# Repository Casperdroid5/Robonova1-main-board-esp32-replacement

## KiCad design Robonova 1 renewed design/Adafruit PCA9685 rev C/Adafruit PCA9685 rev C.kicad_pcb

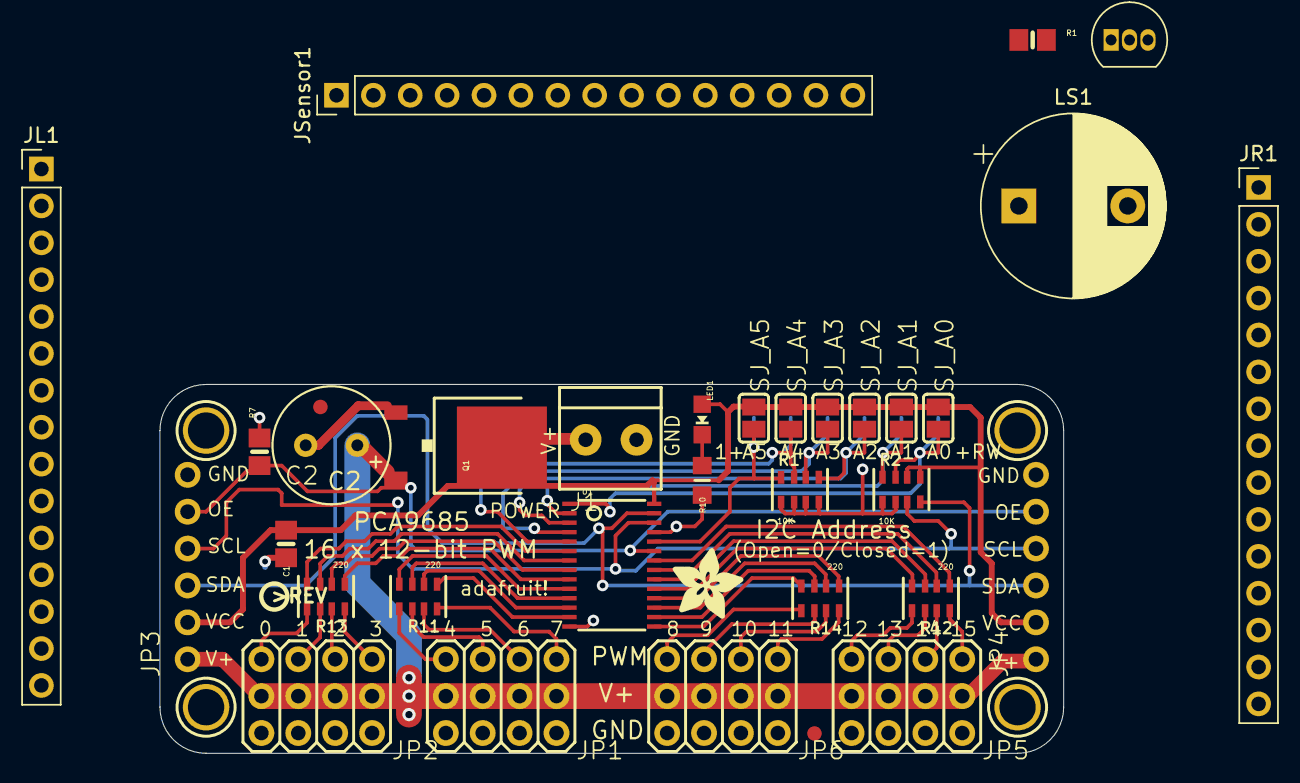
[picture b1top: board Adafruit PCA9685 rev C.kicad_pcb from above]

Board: 2 copper layers, 62.2 x 25.4 mm, 46 parts (0 on the bottom side), 63 nets.

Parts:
C1: 10uF; 0805-NO
C2: CPOL-USE3.5-8; E3,5-8
FID1, FID2: FIDUCIAL; FIDUCIAL_1MM
J1: TERMBLOCK_1X2; TERMBLOCK_1X2-3.5MM
JL1: Conn_01x15_Male; PinHeader_1x15_P2.54mm_Vertical
JP1, JP2, JP5, JP6: HEADER-3X04; 3X04
JP3, JP4: PINHD-1X6CB; 1X06-CLEANBIG
JR1: Conn_01x15_Male; PinHeader_1x15_P2.54mm_Vertical
JSensor1: Conn_01x15_Male; PinHeader_1x15_P2.54mm_Vertical
LED1: GREEN; CHIPLED_0805_NOOUTLINE
LS1: Speaker; CP_Radial_D12.5mm_P7.50mm
Q1: AOD417; TO252
Q2: BC547; TO-92_Inline
R1: 1K; 0805-NO
R1#2, R2: 10K; RESPACK_4X0603
R7: 10K; 0805-NO
R10: 470; _0805MP
R11, R12, R13, R14: 220; RESPACK_4X0603
SJ_A0, SJ_A1, SJ_A2, SJ_A3, SJ_A4, SJ_A5: SOLDERJUMPERREFLOW_NOPASTE; SOLDERJUMPER_REFLOW_NOPASTE
TP1, TP2, TP3, TP4, TP5, TP6: TESTPOINTROUND1MM; TESTPOINT_ROUND_1MM
U1: PCA9685; TSSOP28
U$47, U$48, U$49, U$50: MOUNTINGHOLE2.5; MOUNTINGHOLE_2.5_PLATED
U$51: ADAFRUIT_5MM
U$54: PCBFEAT-REV-040

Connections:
5.0V: C2.+, JP1.2, JP1.5, JP1.8, JP1.11, JP2.2, JP2.5, JP2.8, JP2.11, JP3.1, JP4.1, JP5.2, JP5.5, JP5.8, JP5.11, JP6.2, JP6.5, JP6.8, JP6.11, Q1.2
/3.3V: JL1.1, JSensor1.2, LS1.2
/A0: R2.7, SJ_A0.2, TP6.P$1, U1.1
/A1: R2.8, SJ_A1.2, TP5.P$1, U1.2
/A2: R1#2.5, SJ_A2.2, TP4.P$1
/A3: R1#2.6, SJ_A3.2, TP3.P$1
/A4: R1#2.7, SJ_A4.2, TP2.P$1
/A5: R1#2.8, SJ_A5.2, TP1.P$1
/CLK: JR1.5, JSensor1.9
/CS: JL1.3, JSensor1.10
/D2: JL1.4, JSensor1.6
/D4: JL1.5, JSensor1.5
/D18: JL1.9, JSensor1.11
/D19: JL1.10, JSensor1.12
/D23: JL1.15, JSensor1.13
/D25: JR1.8, JSensor1.14
/D26: JR1.7, JSensor1.15
/MISO: JR1.4, JSensor1.8
/MOSI: JR1.3, JSensor1.7
/OE: JP3.5, JP4.5, R7.1, U1.23
/PWM0: R13.4, U1.6
/PWM1: R13.3, U1.7
/PWM2: R13.2, U1.8
/PWM3: R13.1, U1.9
/PWM4: R11.4, U1.10
/PWM5: R11.3, U1.11
/PWM6: R11.2, U1.12
/PWM7: R11.1, U1.13
/PWM8: R14.4, U1.15
/PWM9: R14.3, U1.16
/PWM10: R14.2, U1.17
/PWM11: R14.1, U1.18
/PWM12: R12.4, U1.19
/PWM13: R12.3, U1.20
/PWM14: R12.2, U1.21
/PWM15: R12.1, U1.22
/Piezo: JR1.6, R1.2
/SCL: JP3.4, JP4.4, R2.3, U1.26
/SCL1: JR1.10, JSensor1.3
/SDA: JP3.3, JP4.3, R2.4, U1.27
/SDA1: JR1.9, JSensor1.4
GND: C1.2, C2.-, J1.2, JL1.2, JP1.3, JP1.6, JP1.9, JP1.12, JP2.3, JP2.6, JP2.9, JP2.12, JP3.6, JP4.6, JP5.3, JP5.6, JP5.9, JP5.12, JP6.3, JP6.6, JP6.9, JP6.12, JR1.2, JSensor1.1, Q1.1, Q2.3, R1#2.1, R1#2.2, R1#2.3, R1#2.4, R2.1, R2.2, R7.2, R10.2, U1.14, U1.25
unnamed: J1.1, Q1.3
unnamed: JP1.1, R11.8
unnamed: JP1.4, R11.7
unnamed: JP1.7, R11.6
unnamed: JP1.10, R11.5
unnamed: JP2.1, R13.8
unnamed: JP2.4, R13.7
unnamed: JP2.7, R13.6
unnamed: JP2.10, R13.5
unnamed: JP5.1, R12.8
unnamed: JP5.4, R12.7
unnamed: JP5.7, R12.6
unnamed: JP5.10, R12.5
unnamed: JP6.1, R14.8
unnamed: JP6.4, R14.7
unnamed: JP6.7, R14.6
unnamed: JP6.10, R14.5
unnamed: LED1.C, R10.1
unnamed: LS1.1, Q2.1
unnamed: Q2.2, R1.1
VCC: C1.1, JP3.2, JP4.2, LED1.A, R2.5, R2.6, SJ_A0.1, SJ_A1.1, SJ_A2.1, SJ_A3.1, SJ_A4.1, SJ_A5.1, U1.28

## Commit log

2022-03-22 Add files via upload
    Firs commit of project. Nowhere near done.
2022-04-07 Some household changes.
2022-04-08 Global pcb layout sketch and obtained data
2022-05-05 Overdischarge protection circuit toegevoegd
2022-06-03 add servo picture
2022-08-11 cleanup
2022-08-11 cleanup and start of schematic
2022-08-11 started gyroscope schematic
2022-08-12 finished imu schematic
2022-08-12 started overdischarge protection circuit design
2022-08-20 started usb-C power connector schematic
2022-08-20 changed usb-c connector, started on mcu power regulator and cleaned up
2022-09-17 Removed useless files and added some libraries to kicad
2025-08-07 removed crap. but probably abondoning this project
    no time, not that excited atm
